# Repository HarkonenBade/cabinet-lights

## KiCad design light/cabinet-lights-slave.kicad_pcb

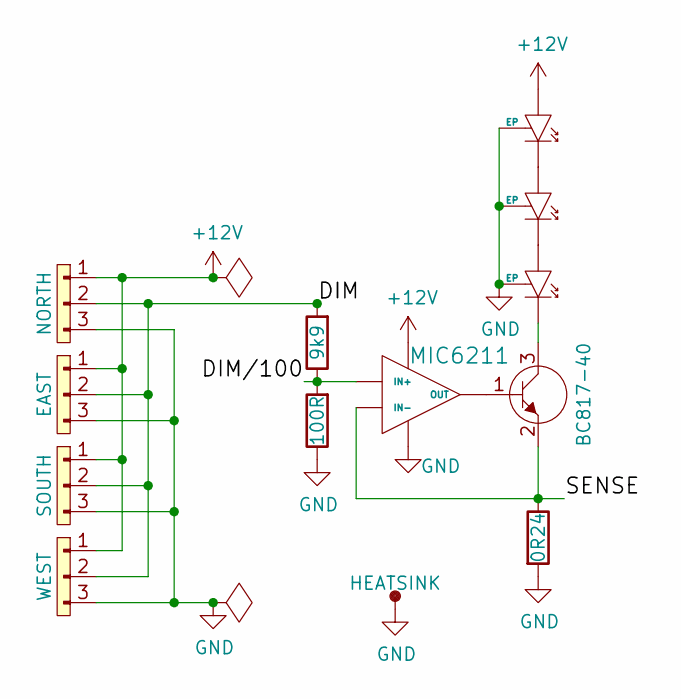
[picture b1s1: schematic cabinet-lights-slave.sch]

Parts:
D1, D2, D3: XLAMP-MX-3; Farnell 1855576
HS1: HEATSINK; 25mm_heatsink; Farnell 1373299
J1: NORTH; S3B-XH-A; Farnell 1516290
J2: EAST; S3B-XH-A; Farnell 1516290
J3: SOUTH; S3B-XH-A; Farnell 1516290
J4: WEST; S3B-XH-A; Farnell 1516290
OP1: MIC6211; SOT-23-5; Farnell 2510411
Q1: BC817-40; SOT-23; Farnell 1798081
R1: 9k9; 0603
R2: 100R; 0603
R3: 0R24; 0603; Farnell 2328092

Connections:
+12V: D1.2, J1.1, J2.1, J3.1, J4.1, OP1.5
/DIM: J1.2, J2.2, J3.2, J4.2, R1.2
/DIM/100: OP1.3 (IN+), R1.1, R2.2
/SENSE: OP1.4 (IN-), Q1.2 (E), R3.1
GND: D1.3 (EP), D2.3 (EP), D3.3 (EP), HS1.1, J1.3, J2.3, J3.3, J4.3, OP1.2, R2.1, R3.2
unnamed: D1.1, D2.2
unnamed: D2.1, D3.2
unnamed: D3.1, Q1.3 (C)
unnamed: OP1.1 (OUT), Q1.1 (B)

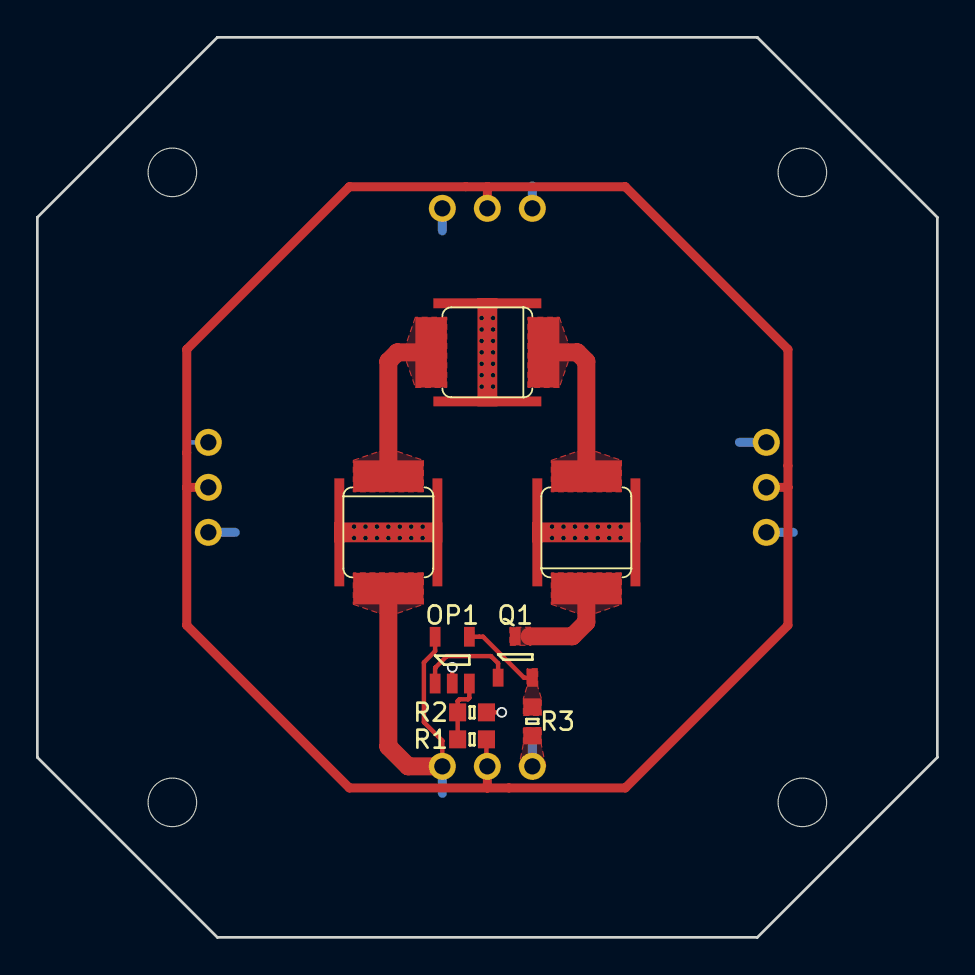
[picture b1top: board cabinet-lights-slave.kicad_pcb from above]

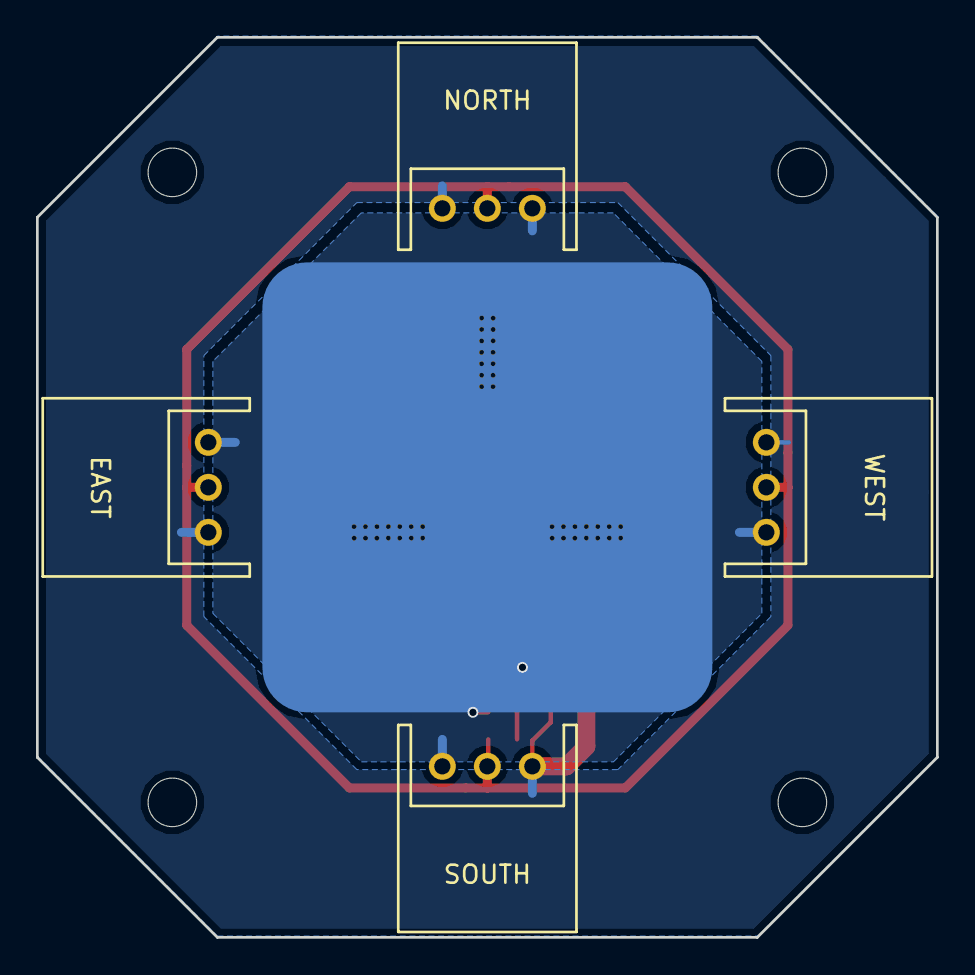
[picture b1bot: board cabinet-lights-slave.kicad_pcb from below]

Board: 2 copper layers, 50.0 x 50.0 mm, 17 parts (5 on the bottom side), 9 nets.

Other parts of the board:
X1, X2, X3, X4: MOUNT; MountingHole_2.7mm_M2.5

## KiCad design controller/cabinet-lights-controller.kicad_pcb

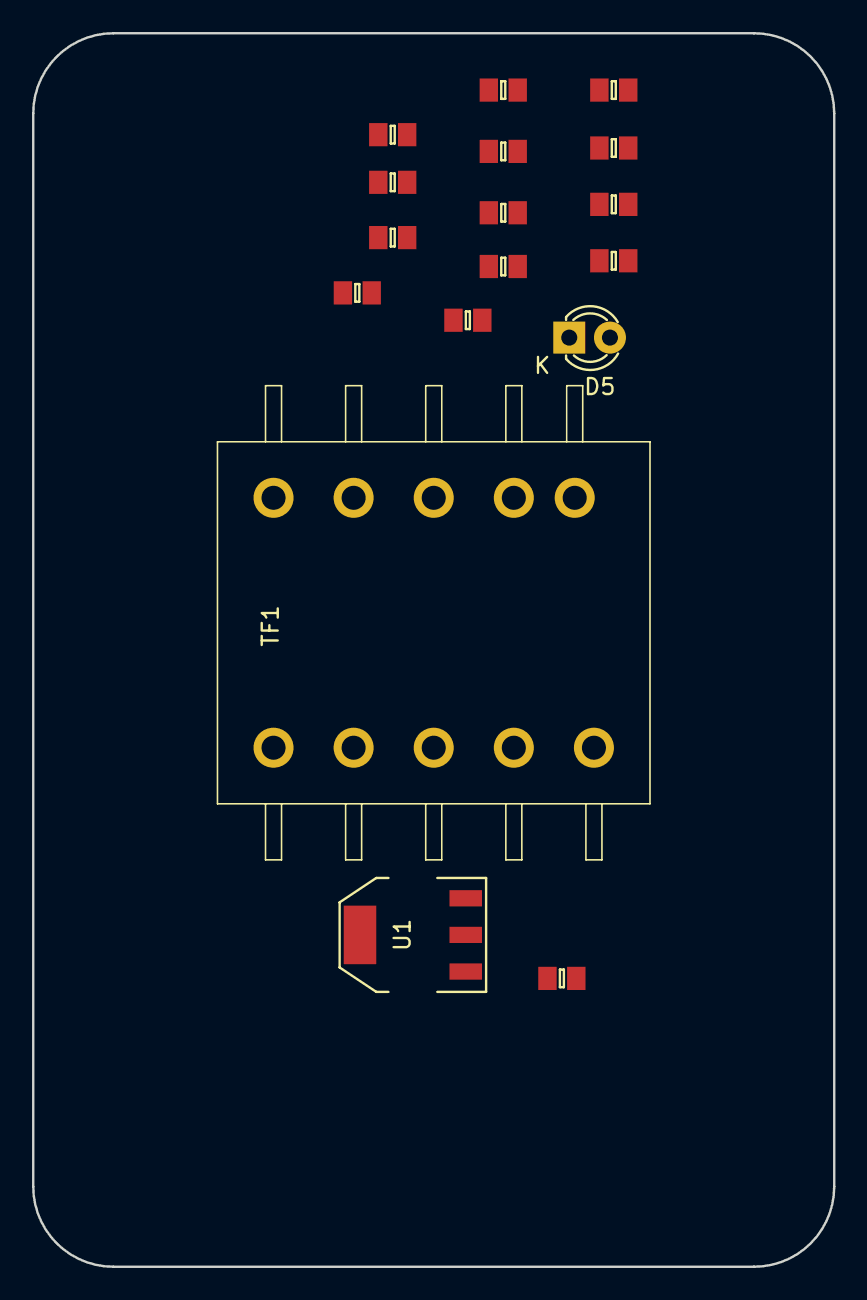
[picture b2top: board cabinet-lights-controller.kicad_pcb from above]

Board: 2 copper layers, 50.0 x 77.0 mm, 17 parts (0 on the bottom side), 14 nets, no tracks yet.

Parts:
D5: PWR; LED-3MM
R2, R3: 5k6; 0805
R4, R5: 3m3; 0805
R6: 2k7; 0805
R8: 10R; 0805
R9: 1k; 0805
R10, R13, R14, R16: 10k; 0805
R11: 47R; 0805
R12: 21k5; 0805
R15: R; 0805
TF1: W750313861
U1: NCP1077; SOT-223

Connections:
+12V: R9.2, R13.2
GND: D5.1, R14.1, TF1.1
GNDPWR: TF1.6, U1.4
unnamed: R2.1, R4.2
unnamed: R3.2, R5.1
unnamed: R6.1, U1.1
unnamed: R13.1, R14.2
unnamed: TF1.10, U1.3
unnamed: R11.2, TF1.5
unnamed: D5.2, R16.2
unnamed: R15.1, R16.1
unnamed: R4.1, R5.2
unnamed: R10.1, R12.1
unnamed: R9.1, R10.2

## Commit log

2016-07-04 Init
2016-07-04 Initial design thoughts.
2016-07-04 Initial Schematics
2016-07-05 More schematic wrangling
    Parts for light module
    Initial PCB for light module
2016-07-06 Models for LED and JST conn, slight PCB shuffle
2016-07-06 Part for pot, transistor driver due to current limits
2016-07-06 Many model shenanigans
2016-07-06 Tweak to use BJT transistor
2016-07-07 Mounting holes, some track shenanigans
2016-07-12 Adding more bits for the controller
2016-07-12 Slowly adding part-nos and footprints for controller
